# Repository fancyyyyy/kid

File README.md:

# kid
6hp trianlge-core vco

No transistor matching, tune it in the same way as you would every other expo converter of this style. There's lots of info on how to tune an analogue oscillator that's better written than I will ever do.

Trim the sine by ear, or use a signal analyser to trim out the 3rd harmonic with R27. R29 has minimal effect, so don't drive yourself mad with it.

The saw trims trim out the bump in the saw, plug it into a scope and trim until you're happy.

Seat the tempco in contact with the sot363-6 transistor pair and stick some thermal paste on top of them.

This is largely an adaptation of the stroh pico vco with some changes to the expo converter.

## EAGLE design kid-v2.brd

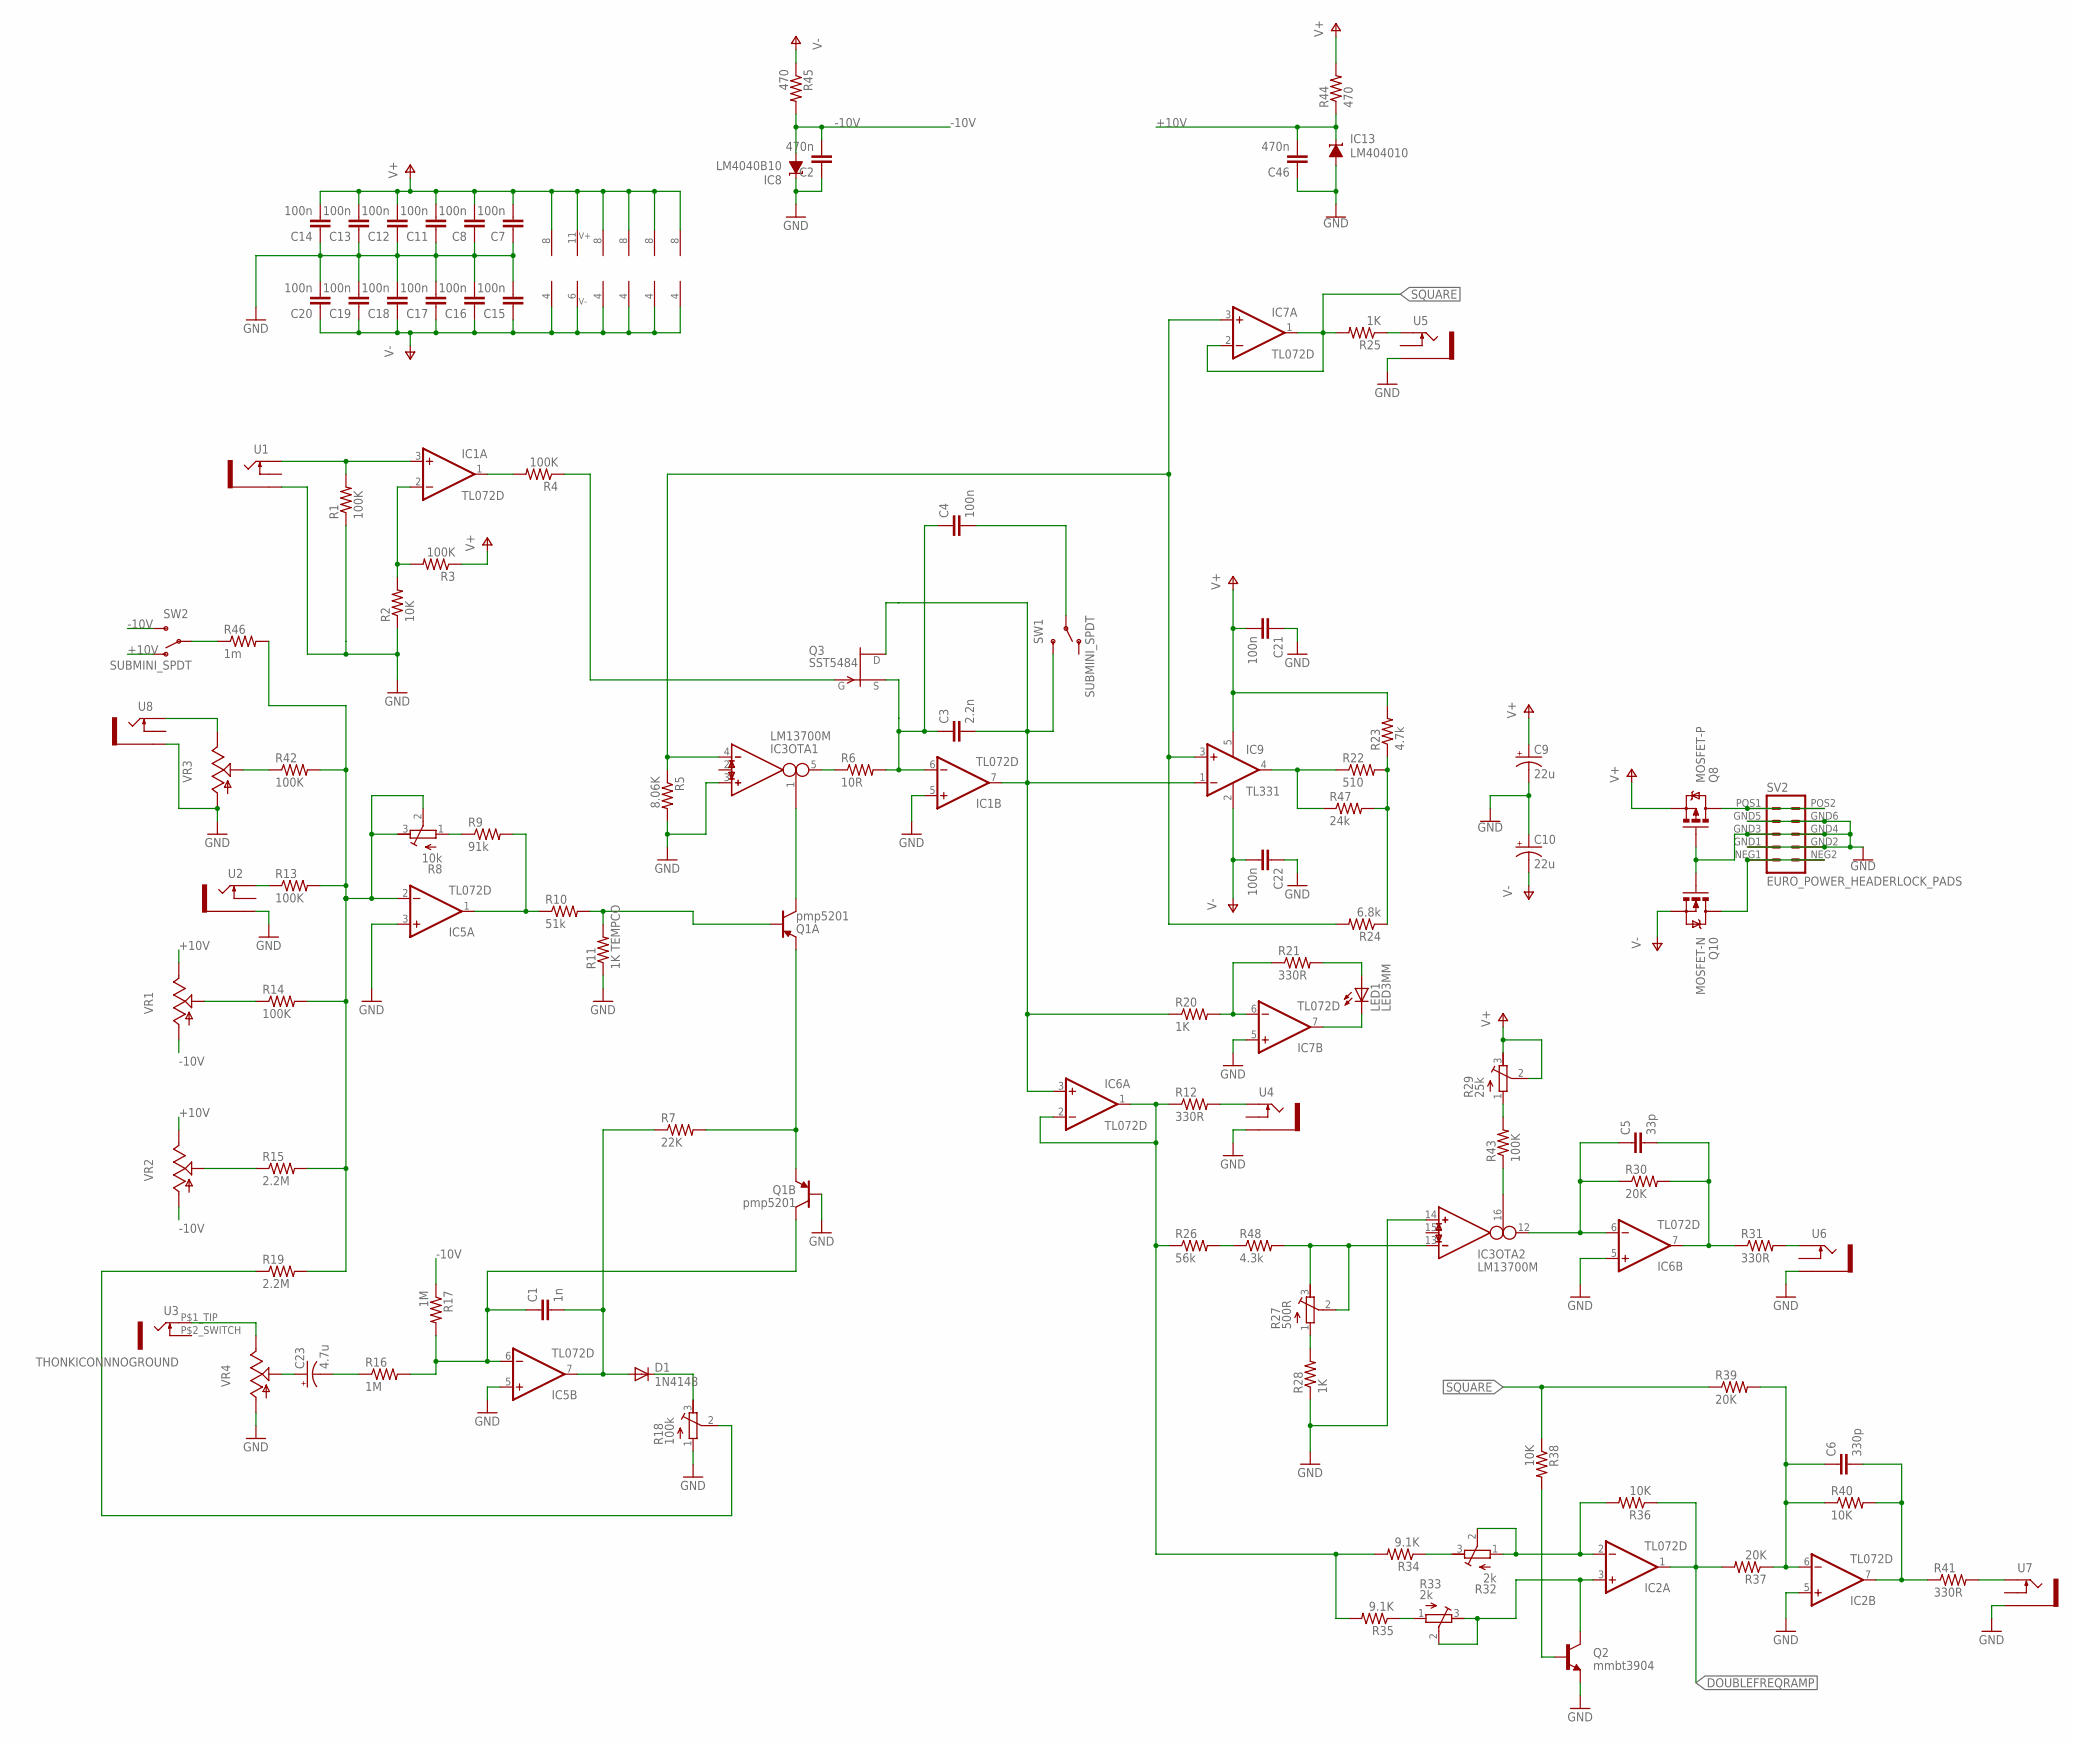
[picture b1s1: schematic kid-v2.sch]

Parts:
C1: 1n; C0603
C2, C46: 470n; 0603-CAP
C3: 2.2n; C0603
C4, C7, C8, C11, C12, C13, C14, C15, C16, C17, C18, C19, C20, C21, C22: 100n; C0603
C5: 33p; C0603
C6: 330p; C0603
C9, C10: 22u; PANASONIC_C
C23: 4.7u; PANASONIC_B
D1: 1N4148; SOD-323
IC1, IC2, IC5, IC6, IC7: TL072D; SO08
IC3: LM13700M; SO16
IC8: LM4040B10; DBZ_R-PDSO-G3
IC9: TL331; DBV-R-PDSO-G5
IC13: LM404010; DBZ_R-PDSO-G3
LED1: LED3MM
Q1: pmp5201; SOT363
Q2: mmbt3904; SOT23
Q3: SST5484; SOT23
Q8: MOSFET-P; SOT23-3
Q10: MOSFET-N; SOT23-3
R1, R3, R4, R13, R14, R42, R43: 100K; R0603
R2, R36, R38, R40: 10K; R0603
R5: 8.06K; R0603
R6: 10R; R0603
R7: 22K; R0603
R8: 10k; RTRIM3296W
R9: 91k; R0603
R10: 51k; R0603
R11: 1K TEMPCO; R0805
R12, R21, R31, R41: 330R; R0603
R15, R19: 2.2M; R0603
R16, R17: 1M; R0603
R18: 100k; RTRIM3296W
R20, R25, R28: 1K; R0603
R22: 510; R0603
R23: 4.7k; R0603
R24: 6.8k; R0603
R26: 56k; R0603
R27: 500R; RTRIM3296W
R29: 25k; RTRIM3296W
R30, R37, R39: 20K; R0603
R32, R33: 2k; RTRIM3296W
R34, R35: 9.1K; R0603
R44: 470; 0603-RES
R45: 470; R0603
R46: 1m; R0603
R47: 24k; R0603
R48: 4.3k; R0603
SV2: EURO_POWER_HEADERLOCK_PADS; EURO_PWR_HEADER_LOCK
SW1, SW2: SUBMINI_SPDT; SUBMINI_TOGGLE
U1, U2, U4, U5, U6, U7, U8: THONKICONNNEW; WQP-PJ301M-12_JACK
U3: THONKICONNNOGROUND
VR1, VR2, VR3, VR4: 9MM_SNAP-IN_POT_; 9MM_SNAP-IN_POT

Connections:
+10V: C46.2, IC13.1 (C), R44.1, SW2.1 (O), VR1.3 (E), VR2.3 (E)
-10V: C2.2, IC8.2 (A), R17.1, R45.2, SW2.3 (S), VR1.1 (A), VR2.1 (A)
DOUBLEFREQRAMP: IC2.1 (OUT), R36.1, R37.2
GND: C2.1, C7.1, C8.1, C9.-, C10.+, C11.1, C12.1, C13.1, C14.1, C15.2, C16.2, C17.2, C18.2, C19.2, C20.2, C21.1, C22.1, C46.1, IC1.5 (+IN), IC2.5 (+IN), IC3.3 (IN_P), IC3.14 (IN_P), IC5.3 (+IN), IC5.5 (+IN), IC6.5 (+IN), IC7.5 (+IN), IC8.1 (C), IC13.2 (A), Q1.P$2 (B), Q2.2 (E), Q8.1 (G), Q10.1 (G), R1.1, R2.1, R5.2, R11.1, R18.1 (A), R28.1, SV2.GND1 (4), SV2.GND2 (3), SV2.GND3 (6), SV2.GND4 (5), SV2.GND5 (8), SV2.GND6 (7), U1.P$3_SLEEVE (SLEEVE), U2.P$3_SLEEVE (SLEEVE), U4.P$3_SLEEVE (SLEEVE), U5.P$3_SLEEVE (SLEEVE), U6.P$3_SLEEVE (SLEEVE), U7.P$3_SLEEVE (SLEEVE), U8.P$3_SLEEVE (SLEEVE), VR3.1 (A), VR4.1 (A)
unnamed: IC1.3 (+IN), R1.2, U1.P$1_TIP (TIP)
unnamed: R26.2, R48.1
unnamed: IC1.2 (-IN), R2.2, R3.2
unnamed: IC3.4 (IN_N), IC7.3 (+IN), IC9.3 (+IN), R5.1, R24.2
unnamed: IC1.1 (OUT), R4.2
unnamed: IC3.5 (OUT), R6.1
unnamed: C3.1, C4.1, IC1.6 (-IN), Q3.2 (S), R6.2
unnamed: IC3.1 (I_BIAS), Q1.P$6 (C)
unnamed: Q1.P$4 (E), Q1.P$5 (E), R7.2
unnamed: Q1.P$1 (B), R10.2, R11.2
unnamed: IC5.1 (OUT), R9.2, R10.1
unnamed: R15.1, VR2.2 (S)
unnamed: Q3.3 (G), R4.1
unnamed: R14.1, VR1.2 (S)
unnamed: R13.1, U2.P$1_TIP (TIP)
unnamed: C1.1, IC5.6 (-IN), Q1.P$3 (C), R16.2, R17.2
unnamed: C23.+, VR4.2 (S)
unnamed: C23.-, R16.1
unnamed: C1.2, D1.2 (A), IC5.7 (OUT), R7.1
unnamed: D1.1 (C), R18.3 (E)
unnamed: R18.2 (S), R19.1
unnamed: U3.P$1_TIP (2), VR4.3 (E)
unnamed: C3.2, IC1.7 (OUT), IC6.3 (+IN), IC9.1 (-IN), Q3.1 (D), R20.1, SW1.3 (S)
unnamed: C4.2, SW1.COM (COMMON)
unnamed: IC3.13 (IN_N), R27.2 (S), R27.3 (E), R48.2
unnamed: IC6.1 (OUT), IC6.2 (-IN), R12.1, R26.1, R34.2, R35.2
unnamed: R12.2, U4.P$1_TIP (TIP)
unnamed: IC7.7 (OUT), LED1.K (C)
unnamed: IC7.6 (-IN), R20.2, R21.1
unnamed: LED1.A, R21.2
unnamed: R25.1, U5.P$1_TIP (TIP)
unnamed: IC5.2 (-IN), R8.2 (S), R8.3 (E), R13.2, R14.2, R15.2, R19.2, R42.2, R46.2
unnamed: R22.2, R23.1, R24.1, R47.2
unnamed: R27.1 (A), R28.2
unnamed: U8.P$1_TIP (TIP), VR3.3 (E)
unnamed: C5.1, IC3.12 (OUT), IC6.6 (-IN), R30.1
unnamed: R29.1 (A), R43.2
unnamed: R32.3 (E), R34.1
unnamed: R33.1 (A), R35.1
unnamed: C5.2, IC6.7 (OUT), R30.2, R31.1
unnamed: IC2.3 (+IN), Q2.3 (C), R33.2 (S), R33.3 (E)
unnamed: R31.2, U6.P$1_TIP (TIP)
unnamed: IC2.2 (-IN), R32.1 (A), R32.2 (S), R36.2
unnamed: Q2.1 (B), R38.2
unnamed: C6.2, IC2.7 (OUT), R40.2, R41.1
unnamed: R41.2, U7.P$1_TIP (TIP)
unnamed: IC3.16 (I_BIAS), R43.1
unnamed: R42.1, VR3.2 (S)
unnamed: R46.1, SW2.COM (COMMON)
unnamed: IC9.4 (OUT), R22.1, R47.1
unnamed: Q8.3 (D), SV2.POS1 (10), SV2.POS2 (9)
unnamed: R8.1 (A), R9.1
unnamed: Q10.3 (D), SV2.NEG1 (2), SV2.NEG2 (1)
REGSAW: C6.1, IC2.6 (-IN), R37.1, R39.2, R40.1
SQUARE: IC7.1 (OUT), IC7.2 (-IN), R25.2, R38.1, R39.1
V+: C7.2, C8.2, C9.+, C11.2, C12.2, C13.2, C14.2, C21.2, IC1.8 (V+), IC2.8 (V+), IC3.11 (V+), IC5.8 (V+), IC6.8 (V+), IC7.8 (V+), IC9.5 (V+), Q8.2 (S), R3.1, R23.2, R29.2 (S), R29.3 (E), R44.2
V-: C10.-, C15.1, C16.1, C17.1, C18.1, C19.1, C20.1, C22.2, IC1.4 (V-), IC2.4 (V-), IC3.6 (V-), IC5.4 (V-), IC6.4 (V-), IC7.4 (V-), IC9.2 (GND), Q10.2 (S), R45.1

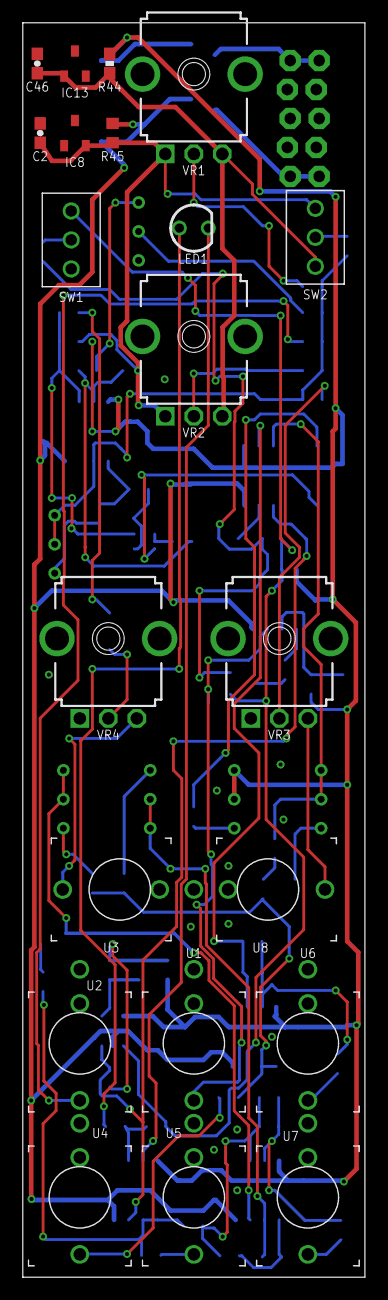
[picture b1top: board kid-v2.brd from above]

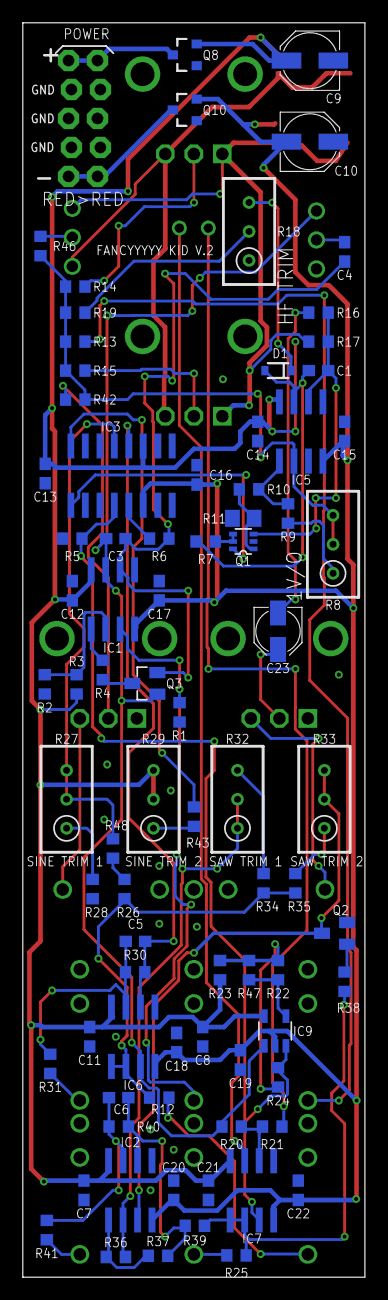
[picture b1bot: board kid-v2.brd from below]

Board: 2 copper layers, 30.0 x 110.0 mm, 103 parts (82 on the bottom side), 61 nets.

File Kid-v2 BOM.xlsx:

Qty | Value | Package | Index | Description | Mouser / Thonk | Notes
Resistors
1.0 | 10R | R0603 | R6 | RESISTOR, American symbol
4.0 | 330R | R0603 | R12 R21 R31 R41 | RESISTOR, American symbol
2.0 | 470R | R0603 | R44 R45 | RESISTOR, American symbol
1.0 | 510R | R0603 | R22 | RESISTOR, American symbol
3.0 | 1K | R0603 | R20 R25 R28 | RESISTOR, American symbol
1.0 | 1K TEMPCO | R0805 | R11 | RESISTOR, American symbol | LT732ATTD102J3600 | Use a normal 0805 1k if u dgaf about western tuning
1.0 | 4.3k | R0603 | R48 | RESISTOR, American symbol
1.0 | 4.7k | R0603 | R23 | RESISTOR, American symbol
1.0 | 6.8k | R0603 | R24 | RESISTOR, American symbol
1.0 | 8.06K | R0603 | R5 | RESISTOR, American symbol
2.0 | 9.1K | R0603 | R34 R35 | RESISTOR, American symbol
4.0 | 10K | R0603 | R2 R36 R38 R40 | RESISTOR, American symbol
3.0 | 20K | R0603 | R30 R37 R39 | RESISTOR, American symbol
1.0 | 22K | R0603 | R7 | RESISTOR, American symbol
1.0 | 24k | R0603 | R47 | RESISTOR, American symbol
1.0 | 51k | R0603 | R10 | RESISTOR, American symbol
1.0 | 56k | R0603 | R26 | RESISTOR, American symbol
1.0 | 91k | R0603 | R9 | RESISTOR, American symbol
7.0 | 100K | R0603 | R1 R3 R4 R13 R14 R42 R43 | RESISTOR, American symbol
3.0 | 1M | R0603 | R16 R17 R46 | RESISTOR, American symbol
2.0 | 2.2M | R0603 | R15 R19 | RESISTOR, American symbol
Capacitors
1.0 | 33p | C0603 | C5 | CAPACITOR, European symbol
1.0 | 330p | C0603 | C6 | CAPACITOR, European symbol
1.0 | 1n | C0603 | C1 | CAPACITOR, European symbol
1.0 | 2.2n | C0603 | C3 | CAPACITOR, European symbol |  | NPO / COG timing cap
15.0 | 100n | C0603 | C4 C7 C8 C11 C12 C13 C14 C15 C16 C17 C18 C19 C20 C21 C22 | CAPACITOR, European symbol
2.0 | 470n | 0603-CAP | C2, C46 | CAPACITOR, European symbol
1.0 | 4.7u | PANASONIC_B | C23 | POLARIZED CAPACITOR, American symbol |  | AC coupling cap for linfm, bridge this if you don't care
2.0 | 22u | PANASONIC_C | C9, C10 | POLARIZED CAPACITOR, American symbol
Hardware
1.0 | 500R | RTRIM3296W | R27 | Trimm resistor | Tayda
2.0 | 2k | RTRIM3296W | R32 R33 | Trimm resistor | Tayda
1.0 | 10k | RTRIM3296W | R8 | Trimm resistor | Tayda
1.0 | 25k | RTRIM3296W | R29 | Trimm resistor | Tayda
1.0 | 100k | RTRIM3296W | R18 | Trimm resistor | Tayda
1.0 | LED3MM | LED3MM | LED1 |  | https://www.mouser.co.uk/ProductDetail/604-WP937EGW | bi-colour if you want
1.0 | EURO_POWER_HEADER | EURO_PWR_HEADER_LOCK | SV2 | Power Header
1.0 | SUBMINI_SPDT ON-ON | SUBMINI_TOGGLE | SW1 |  | https://www.thonk.co.uk/shop/sub-mini-toggle-switches/ | ON-ON
1.0 | SUBMINI_SPDT ON-OFF-ON | SUBMINI_TOGGLE | SW2 |  | https://www.thonk.co.uk/shop/sub-mini-toggle-switches/ | ON-OFF-ON
8.0 | THONKICONNNEW | WQP-PJ301M-12_JACK | U1, U2, U3, U4, U5, U6, U7, U8 | 3.5mm socket for Eurorack modular synths | https://www.thonk.co.uk/shop/thonkiconn/
2.0 |  | 9MM_SNAP-IN_POT | VR1, VR2 | 9mm vertical snap-in pot, Alpha / Panasonic style | https://www.thonk.co.uk/shop/alpha-9mm-pots/ | Course & Fine
2.0 |  | 9MM_TALL-TRIM-POT | VR3, VR4 |  | https://www.thonk.co.uk/product-category/parts/pot/9mm/9mm-t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 | FM Attenuation
Semi
1.0 | 1N4148 | SOD-323 | D1 | Diode | 1N4148WS
1.0 | LM13700M | SO16 | IC3 | Dual OTA with buffers
2.0 | LM4040C10 | SOT23-3 | IC8 IC13 | PRECISION MICROPOWER SHUNT VOLTAGE REFERENCE | LM4040CIM3-10.0/NOPB | The higher class regulators you use, the better the octave switch is - C is fine
1.0 | MOSFET-N | SOT23-3 | Q10 |  | DMN3023L-7 | Reverse power protection, there are cheaper options if you wanna look - none in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
1.0 | MOSFET-P | SOT23-3 | Q8 |  | DMP3099L-7 | Don't use diodes, for reverse protection - the drop is too much for 10v reg
1.0 | MMBFJ310 | SOT23-3 | Q3 | N-Channel JFETs | MMBFJ310 | Other fets could work here
5.0 | TL072D | SO08 | IC1, IC2, IC5, IC6, IC7 | OP AMP
1.0 | TL331 | SOT23-5 | IC9 | SINGLE DIFFERENTIAL COMPARATOR | TL331KDBVR
1.0 | mmbt3904 | SOT23-3 | Q2 | Transistor NPN | MMBT3904-7-F
1.0 | pmp5201 | SOT-363-6 | Q1 |  | PMP5201Y,115 | Put in contact with the 1k tempco, smear some thermal paste on top. You could t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

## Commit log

2018-11-23 Add files via upload
    Updated silkscreen

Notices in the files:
parts and their libraries:
SparkFun-PowerSymbols: Licensing: Creative Commons ShareAlike 4.0 International - https://creativecommons.org/licenses/by-sa/4.0
